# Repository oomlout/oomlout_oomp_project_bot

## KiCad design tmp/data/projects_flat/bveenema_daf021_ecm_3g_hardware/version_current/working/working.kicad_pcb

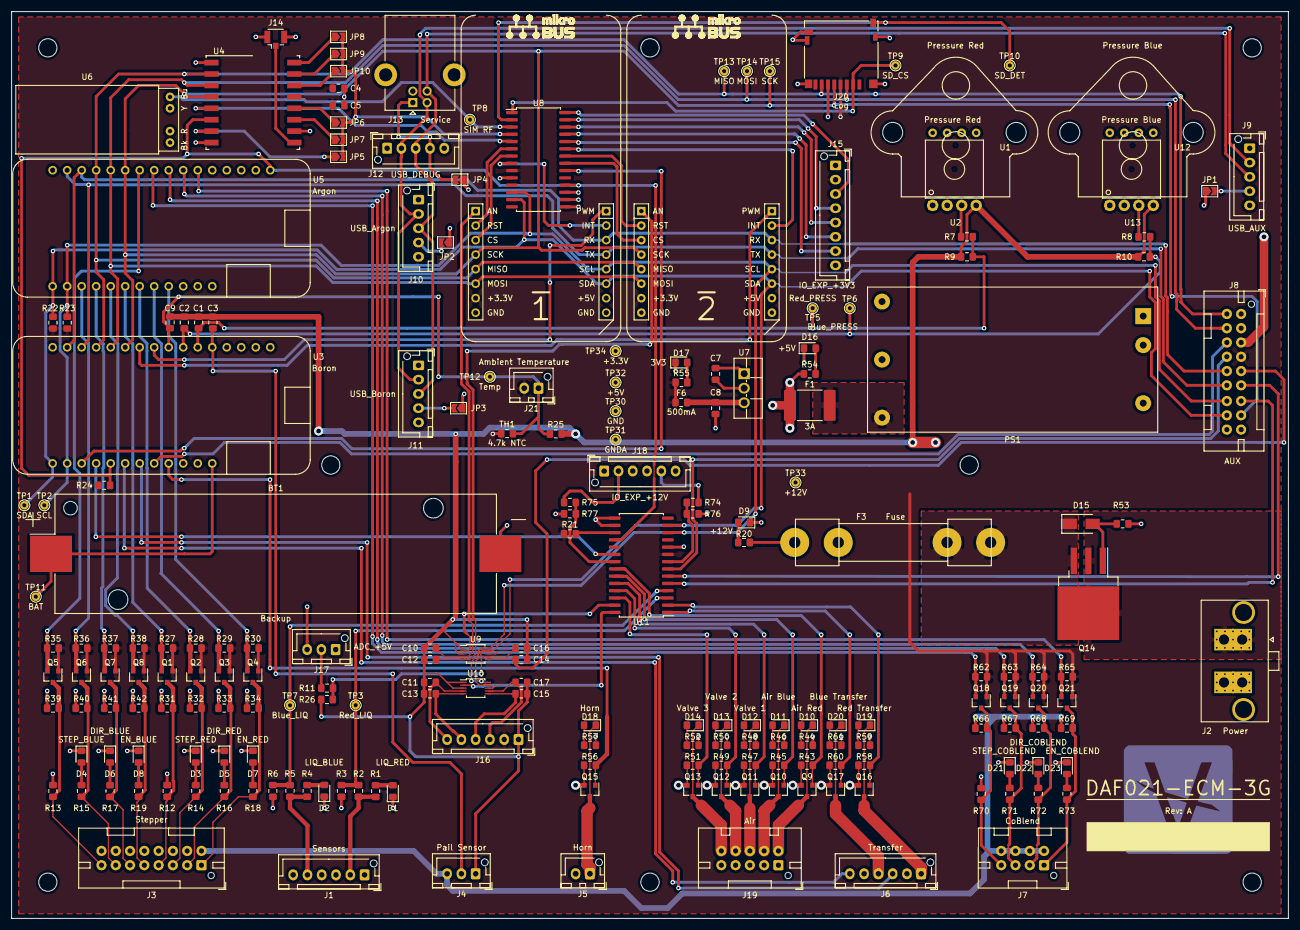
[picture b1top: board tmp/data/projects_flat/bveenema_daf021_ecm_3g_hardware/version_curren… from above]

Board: 4 copper layers, 223.5 x 158.8 mm, 207 parts (0 on the bottom side), 138 nets.

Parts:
BT1: Backup; BatteryHolder_Keystone_1042_1x18650
C1, C2, C3, C4, C9, C10, C11, C12, C13, C14, C15, C16, C17: 0.1uF; C_0805_2012Metric_Pad1.15x1.40mm_HandSolder
C5, C8: 10uF; C_0805_2012Metric_Pad1.15x1.40mm_HandSolder
C7: 2.2uF; C_0805_2012Metric_Pad1.15x1.40mm_HandSolder
D1: LIQ_RED; LED_0805_2012Metric_Pad1.15x1.40mm_HandSolder
D2: LIQ_BLUE; LED_0805_2012Metric_Pad1.15x1.40mm_HandSolder
D3: STEP_RED; LED_0805_2012Metric_Pad1.15x1.40mm_HandSolder
D4: STEP_BLUE; LED_0805_2012Metric_Pad1.15x1.40mm_HandSolder
D5: DIR_RED; LED_0805_2012Metric_Pad1.15x1.40mm_HandSolder
D6: DIR_BLUE; LED_0805_2012Metric_Pad1.15x1.40mm_HandSolder
D7: EN_RED; LED_0805_2012Metric_Pad1.15x1.40mm_HandSolder
D8: EN_BLUE; LED_0805_2012Metric_Pad1.15x1.40mm_HandSolder
D9: +12V; LED_0805_2012Metric_Pad1.15x1.40mm_HandSolder
D10: Air Red; LED_0805_2012Metric_Pad1.15x1.40mm_HandSolder
D11: Air Blue; LED_0805_2012Metric_Pad1.15x1.40mm_HandSolder
D12: Valve 1; LED_0805_2012Metric_Pad1.15x1.40mm_HandSolder
D13: Valve 2; LED_0805_2012Metric_Pad1.15x1.40mm_HandSolder
D14: Valve 3; LED_0805_2012Metric_Pad1.15x1.40mm_HandSolder
D15: 10V; D_SMA
D16: +5V; LED_0805_2012Metric_Pad1.15x1.40mm_HandSolder
D17: 3V3; LED_0805_2012Metric_Pad1.15x1.40mm_HandSolder
D18: Horn; LED_0805_2012Metric_Pad1.15x1.40mm_HandSolder
D19: Red Transfer; LED_0805_2012Metric_Pad1.15x1.40mm_HandSolder
D20: Blue Transfer; LED_0805_2012Metric_Pad1.15x1.40mm_HandSolder
D21: STEP_COBLEND; LED_0805_2012Metric_Pad1.15x1.40mm_HandSolder
D22: DIR_COBLEND; LED_0805_2012Metric_Pad1.15x1.40mm_HandSolder
D23: EN_COBLEND; LED_0805_2012Metric_Pad1.15x1.40mm_HandSolder
F1: 3A; Fuse_2920_7451Metric_Pad2.10x5.45mm_HandSolder
F3: Fuse; FUSE_HOLDER_.25inx1.25in_01220093Z
F6: 500mA; Fuse_0805_2012Metric_Pad1.15x1.40mm_HandSolder
J1: Sensors; JST_XH_B6B-XH-AM_1x06_P2.50mm_Vertical
J2: Power; Molex_Sabre_43160-2102_1x02_P7.50mm_Vertical_ThermalVias
J3: Stepper; JST_XAD_B16B-XADSS-N-A_2x08_P2.50mm_Vertical
J4: Pail Sensor; JST_XH_B3B-XH-AM_1x03_P2.50mm_Vertical
J5: Horn; JST_XH_B2B-XH-AM_1x02_P2.50mm_Vertical
J6: Transfer; JST_XH_B6B-XH-AM_1x06_P2.50mm_Vertical
J7: CoBlend; JST_XAD_B08B-XADSS-N-A_2x04_P2.50mm_Vertical
J8: AUX; JST_XAD_B18B-XADSS-N-A_2x09_P2.50mm_Vertical
J9: USB_AUX; JST_XH_B5B-XH-AM_1x05_P2.50mm_Vertical
J10: USB_Argon; JST_XH_B5B-XH-AM_1x05_P2.50mm_Vertical
J11: USB_Boron; JST_XH_B5B-XH-AM_1x05_P2.50mm_Vertical
J12: USB_DEBUG; JST_XH_B5B-XH-AM_1x05_P2.50mm_Vertical
J13: Service; USB_B_Molex_67068-8000_Horizontal
J14: Antenna; U.FL_Hirose_U.FL-R-SMT-1_Vertical
J15: IO_EXP_+3V3; JST_XH_B8B-XH-AM_1x08_P2.50mm_Vertical
J16: ADC_+3V3; JST_XH_B6B-XH-AM_1x06_P2.50mm_Vertical
J17: ADC_+5V; JST_XH_B3B-XH-AM_1x03_P2.50mm_Vertical
J18: IO_EXP_+12V; JST_XH_B6B-XH-AM_1x06_P2.50mm_Vertical
J19: Air; JST_XAD_B10B-XADSS-N-A_2x05_P2.50mm_Vertical
J20: Log; microSD_HC_Hirose_DM3D-SF
J21: Ambient Temperature; JST_XH_B2B-XH-AM_1x02_P2.50mm_Vertical
JP1, JP2, JP3, JP4, JP5, JP6, JP7, JP8, JP9, JP10: Jumper_NO_Small; SolderJumper-2_P1.3mm_Open_TrianglePad1.0x1.5mm
NT1: Net-Tie_2; NetTie-2_SMD_Pad2.0mm
PS1: 12V/5V Converter; MeanWell_Power_Supply_2x1in_Shielded
Q1, Q2, Q3, Q4, Q5, Q6, Q7, Q8, Q9, Q10, Q11, Q12, Q13, Q15, Q16, Q17, Q18, Q19, Q20, Q21: Q_NMOS_GSD; SOT-23
Q14: Q_PMOS_GDS; TO-263-3_TabPin2
R1, R4, R14, R15, R16, R17, R18, R19, R20, R54, R71, R72, R73: 4.7K; R_0805_2012Metric_Pad1.15x1.40mm_HandSolder
R2, R5, R21, R24, R74, R75: 10K; R_0805_2012Metric_Pad1.15x1.40mm_HandSolder
R3, R6, R76, R77: 1.5K; R_0805_2012Metric_Pad1.15x1.40mm_HandSolder
R7, R8, R11: 2.2k 0.5%; R_0805_2012Metric_Pad1.15x1.40mm_HandSolder
R9, R10, R25, R26: 4.7k 0.5%; R_0805_2012Metric_Pad1.15x1.40mm_HandSolder
R12, R13, R55, R70: 1k; R_0805_2012Metric_Pad1.15x1.40mm_HandSolder
R22, R23, R44, R46, R48, R50, R52, R57, R59, R61: 4.7k; R_0805_2012Metric_Pad1.15x1.40mm_HandSolder
R27, R28, R29, R30, R31, R32, R33, R34, R35, R36, R37, R38, R39, R40, R41, R42, R62, R63, R64, R65, R66, R67, R68, R69: 10k; R_0805_2012Metric_Pad1.15x1.40mm_HandSolder
R43, R45, R47, R49, R51, R53, R56, R58, R60: 100k; R_0805_2012Metric_Pad1.15x1.40mm_HandSolder
TH1: 4.7k NTC; R_0805_2012Metric_Pad1.15x1.40mm_HandSolder
TP1: SDA; TestPoint_THTPad_D1.5mm_Drill0.7mm
TP2: SCL; TestPoint_THTPad_D1.5mm_Drill0.7mm
TP3: Red_LIQ; TestPoint_THTPad_D1.5mm_Drill0.7mm
TP5: Red_PRESS; TestPoint_THTPad_D1.5mm_Drill0.7mm
TP6: Blue_PRESS; TestPoint_THTPad_D1.5mm_Drill0.7mm
TP7: Blue_LIQ; TestPoint_THTPad_D1.5mm_Drill0.7mm
TP8: SIM RF; TestPoint_THTPad_D1.5mm_Drill0.7mm
TP9: SD_CS; TestPoint_THTPad_D1.5mm_Drill0.7mm
TP10: SD_DET; TestPoint_THTPad_D1.5mm_Drill0.7mm
TP11: BAT; TestPoint_THTPad_D1.5mm_Drill0.7mm
TP12: Temp; TestPoint_THTPad_D1.5mm_Drill0.7mm
TP13: MISO; TestPoint_THTPad_D1.5mm_Drill0.7mm
TP14: MOSI; TestPoint_THTPad_D1.5mm_Drill0.7mm
TP15: SCK; TestPoint_THTPad_D1.5mm_Drill0.7mm
TP30: GND; TestPoint_THTPad_D1.5mm_Drill0.7mm
TP31: GNDA; TestPoint_THTPad_D1.5mm_Drill0.7mm
TP32: +5V; TestPoint_THTPad_D1.5mm_Drill0.7mm
TP33: +12V; TestPoint_THTPad_D1.5mm_Drill0.7mm
TP34: +3.3V; TestPoint_THTPad_D1.5mm_Drill0.7mm
U1: Pressure Red; HoneyWell_DIP_AN
U2: Pressure Red; HoneyWell_SIP_NB
U3: Boron; Argon_Boron_Xenon
U4: RFM69HCW; HOPERF_RFM69HCW
U5: Argon; Argon_Boron_Xenon
U6: AK-220V-119
U7: 5V/3V3 Regulator; TO-220F-3_Vertical
U8, U11: MCP23017; SOIC-28W_7.5x17.9mm_P1.27mm
U9, U10: ADS1115IDGS; TSSOP-10_3x3mm_P0.5mm
U12: Pressure Blue; HoneyWell_DIP_AN
U13: Pressure Blue; HoneyWell_SIP_NB

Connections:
+3V3: C4.2, C5.2, F6.1, J8.7, J15.2, J16.2, J20.4, J21.2, Q1.1, Q2.1, Q3.1, Q4.1, Q5.1, Q6.1, Q7.1, Q8.1, Q18.1, Q19.1, Q20.1, Q21.1, R21.1, R22.1, R23.1, R24.1, R27.2, R28.2, R29.2, R30.2, R35.2, R36.2, R37.2, R38.2, R55.1, R62.2, R63.2, R64.2, R65.2, TH1.1, TP34.1, U4.13, U8.9, U9.8, U10.8, U11.9
+5V: C7.2, F1.1, J3.2, J3.4, J3.6, J3.8, J3.10, J3.12, J3.14, J3.16, J4.3, J7.2, J7.4, J7.6, J7.8, J8.5, J17.3, JP1.1, JP2.1, JP3.1, JP4.1, R31.1, R32.1, R33.1, R34.1, R39.1, R40.1, R41.1, R42.1, R54.1, R66.1, R67.1, R68.1, R69.1, TP32.1, U1.2, U2.2, U3.26, U5.26, U6.R, U7.1, U12.2, U13.2
+12V: F3.2, J1.3, J1.6, J5.2, J6.2, J6.5, J8.3, J18.3, J18.6, J19.1, J19.3, J19.5, J19.7, J19.9, PS1.1, R20.1, R44.1, R46.1, R48.1, R50.1, R52.1, R57.1, R59.1, R61.1, TP33.1
/Power/VIN: J2.1, Q14.2
/Power/VIN_PROTECT: D15.1, F3.1, Q14.3
/USB(+): J9.3, J10.3, J11.3, J12.3, J13.3
/USB(-): J9.2, J10.2, J11.2, J12.2, J13.2
ADC_1_RDY: U9.2, U11.27
ADC_2_RDY: U10.2, U11.28
AUS_RST: J8.11, U11.6
AUX_AN: C14.2, J8.9, U9.6
AUX_CS: J8.13, U11.5
AUX_INT: J8.8, U11.7
AUX_PWM: J8.6, U3.24
AUX_RX: J8.10, U3.15, U5.14
AUX_TX: J8.12, U3.14, U5.15
Air_Blue_EN: Q10.1, R45.1, U11.23
Air_Blue_GND: D11.1, J19.4, Q10.3
Air_Red_EN: Q9.1, R43.1, U11.22
Air_Red_GND: D10.1, J19.2, Q9.3
Ambient_Temperature: C9.2, J21.1, R25.1, TH1.2, TP12.1, U3.8
Blue_DIR: J3.11, Q7.3, R17.1, R41.2
Blue_DIR_LV: Q7.2, R37.1, U5.20
Blue_EN: J3.9, Q8.3, R19.1, R42.2
Blue_EN_LV: Q8.2, R38.1, U5.21
Blue_STATUS: J3.15, Q5.3, R13.2, R39.2
Blue_STATUS_LV: Q5.2, R35.1, U5.10
Blue_STEP: J3.13, Q6.3, R15.1, R40.2
Blue_STEP_LV: Q6.2, R36.1, U5.19
CoBlend_DIR: J7.3, Q20.3, R68.2, R72.1
CoBlend_DIR_LV: Q20.2, R64.1, U5.7
CoBlend_EN: J7.1, Q21.3, R69.2, R73.1
CoBlend_EN_LV: Q21.2, R65.1, U5.6
CoBlend_STATUS: J7.7, Q18.3, R66.2, R70.2
CoBlend_STATUS_LV: Q18.2, R62.1, U5.9
CoBlend_STEP: J7.5, Q19.3, R67.2, R71.1
CoBlend_STEP_LV: Q19.2, R63.1, U5.8
GND: BT1.2, C4.1, C5.1, C7.1, C8.2, D1.1, D2.1, D3.1, D4.1, D5.1, D6.1, D7.1, D8.1, D9.1, D16.1, D17.1, D21.1, D22.1, D23.1, J1.1, J1.4, J2.2, J8.1, J8.17, J8.18, J9.1, J10.1, J11.1, J12.1, J13.4, J13.5, J14.2, J15.1, J17.1, J18.1, J18.4, J20.6, J20.9, J20.11, NT1.1, PS1.2, PS1.5, Q9.2, Q10.2, Q11.2, Q12.2, Q13.2, Q15.2, Q16.2, Q17.2, R3.2, R6.2, R12.1, R13.1, R43.2, R45.2, R47.2, R49.2, R51.2, R53.2, R56.2, R58.2, R60.2, R70.1, R76.2, R77.2, TP30.1, U3.4, U4.1, U4.8, U4.10, U5.4, U6.Bk, U6.Y, U7.2, U8.10, U8.15, U8.16, U8.17, U11.10, U11.15, U11.16
GNDA: C1.2, C2.2, C3.1, C9.1, C10.1, C11.1, C12.1, C13.1, C14.1, C15.1, C16.1, C17.1, J4.1, J16.1, NT1.2, R9.2, R10.2, R25.2, R26.2, TP31.1, U1.4, U2.4, U9.1, U9.3, U10.1, U10.3, U12.4, U13.4
Horn_EN: Q15.1, R56.1, U3.25
I2C_RESET: R24.2, U3.21, U4.6, U5.1, U8.18, U11.18
IO_2_INT: U3.20, U11.20
IO_INT: U3.19, U8.20
Liquid_Sensor_Blue: R5.2, R6.1, TP7.1, U11.4
Liquid_Sensor_Red: R2.2, R3.1, TP3.1, U11.3
MISO: J8.2, J20.7, TP13.1, U3.13, U4.2, U5.13
MOSI: J8.4, J20.3, TP14.1, U3.12, U4.3, U5.12
unnamed: BT1.1, TP11.1, U3.28
unnamed: C8.1, F6.2, U7.3
unnamed: C11.2, J16.6, U10.4
unnamed: C13.2, J16.5, U10.5
unnamed: C15.2, J16.4, U10.6
unnamed: C16.2, R11.1, R26.1, U9.7
unnamed: C17.2, J16.3, U10.7
unnamed: D1.2, R1.2
unnamed: D2.2, R4.2
unnamed: D3.2, R14.2
unnamed: D4.2, R15.2
unnamed: D5.2, R16.2
unnamed: D6.2, R17.2
unnamed: D7.2, R18.2
unnamed: D8.2, R19.2
unnamed: D9.2, R20.2
unnamed: D10.2, R44.2
unnamed: D11.2, R46.2
unnamed: D12.2, R48.2
unnamed: D13.2, R50.2
unnamed: D14.2, R52.2
unnamed: D15.2, Q14.1, R53.1
unnamed: D16.2, R54.2
unnamed: D17.2, R55.2
unnamed: D18.1, J5.1, Q15.3
unnamed: D18.2, R57.2
unnamed: D19.2, R59.2
unnamed: D20.2, R61.2
unnamed: D21.2, R71.2
unnamed: D22.2, R72.2
unnamed: D23.2, R73.2
unnamed: F1.2, PS1.4
unnamed: J1.2, R1.1, R2.1
unnamed: J1.5, R4.1, R5.1
unnamed: J9.4, JP1.2
unnamed: J10.4, JP2.2
unnamed: J11.4, JP3.2
unnamed: J12.4, J13.1, JP4.2
unnamed: J14.1, U4.9
unnamed: J15.3, U8.28
unnamed: J15.4, U8.27
unnamed: J15.5, U8.26
unnamed: J15.6, U8.25
unnamed: J15.7, U8.24
unnamed: J17.2, R11.2
unnamed: J18.2, R75.1
unnamed: J18.5, R74.1
unnamed: JP5.1, U4.7
unnamed: JP6.1, U4.12
unnamed: JP7.1, U4.11
unnamed: JP8.1, U4.16
unnamed: JP9.1, U4.15
unnamed: JP10.1, U4.14
unnamed: R7.2, U1.3, U2.3
unnamed: R8.2, U12.3, U13.3
unnamed: R21.2, U11.17
unnamed: R74.2, R76.1, U11.8
unnamed: R75.2, R77.1, U11.21
Pail_Sensor: C3.2, J4.2, U3.5
Pressure_Blue: C2.1, R8.1, R10.1, TP6.1, U3.7
Pressure_Red: C1.1, R7.1, R9.1, TP5.1, U3.6
RADIO_CS: U4.5, U8.5
RADIO_INT: JP5.2, JP6.2, JP7.2, JP8.2, JP9.2, JP10.2, U8.4
Red_DIR: J3.3, Q3.3, R16.1, R33.2
Red_DIR_LV: Q3.2, R29.1, U5.24
Red_EN: J3.1, Q4.3, R18.1, R34.2
Red_EN_LV: Q4.2, R30.1, U5.25
Red_STATUS: J3.7, Q1.3, R12.2, R31.2
Red_STATUS_LV: Q1.2, R27.1, U5.22
Red_STEP: J3.5, Q2.3, R14.1, R32.2
Red_STEP_LV: Q2.2, R28.1, U5.23
SCK: J8.15, J20.5, TP15.1, U3.11, U4.4, U5.11
SCL: J8.14, R23.2, TP2.1, U3.18, U5.18, U8.12, U9.10, U10.10, U11.12
SDA: J8.16, R22.2, TP1.1, U3.17, U5.17, U8.13, U9.9, U10.9, U11.13
SD_CS: J20.2, TP9.1, U8.1
SD_DET: J20.10, TP10.1, U8.2
Transfer_Blue_EN: Q17.1, R60.1, U11.1
Transfer_Blue_GND: D20.1, J6.4, Q17.3
Transfer_Blue_Reserved: J6.6, U3.22
Transfer_Red_EN: Q16.1, R58.1, U11.2
Transfer_Red_GND: D19.1, J6.1, Q16.3
Transfer_Red_Reserved: J6.3, U3.23
USER_REMOTE: TP8.1, U6.Bu, U8.3
Valve_1_EN: Q11.1, R47.1, U11.24
Valve_1_GND: D12.1, J19.6, Q11.3
Valve_2_EN: Q12.1, R49.1, U11.25
Valve_2_GND: D13.1, J19.8, Q12.3
Valve_3_EN: Q13.1, R51.1, U11.26
Valve_3_GND: D14.1, J19.10, Q13.3
mikroBUS_1_AN: C10.2, U9.4
mikroBUS_2_AN: C12.2, U9.5

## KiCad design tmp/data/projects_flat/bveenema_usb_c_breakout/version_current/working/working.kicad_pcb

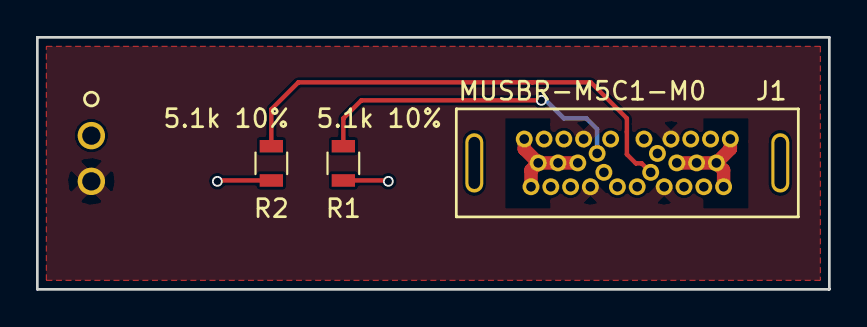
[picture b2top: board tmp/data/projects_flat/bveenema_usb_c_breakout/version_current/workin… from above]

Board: 2 copper layers, 44.0 x 14.0 mm, 4 parts (1 on the bottom side), 4 nets.

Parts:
J1: MUSBR-M5C1-M0; MUSBR-M5C1-X0
J2: 640455-2
R1, R2: 5.1k 10%; R_0805

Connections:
GND: J1.0, J1.A1, J1.A12, J1.B1, J1.B12, J1.G1, J1.G2, J1.G3, J1.G4, J1.G5, J1.G6, J2.1, R1.2, R2.2
unnamed: J1.A5, R1.1
unnamed: J1.B5, R2.1
VCC: J1.A4, J1.A9, J1.B4, J1.B9, J2.2

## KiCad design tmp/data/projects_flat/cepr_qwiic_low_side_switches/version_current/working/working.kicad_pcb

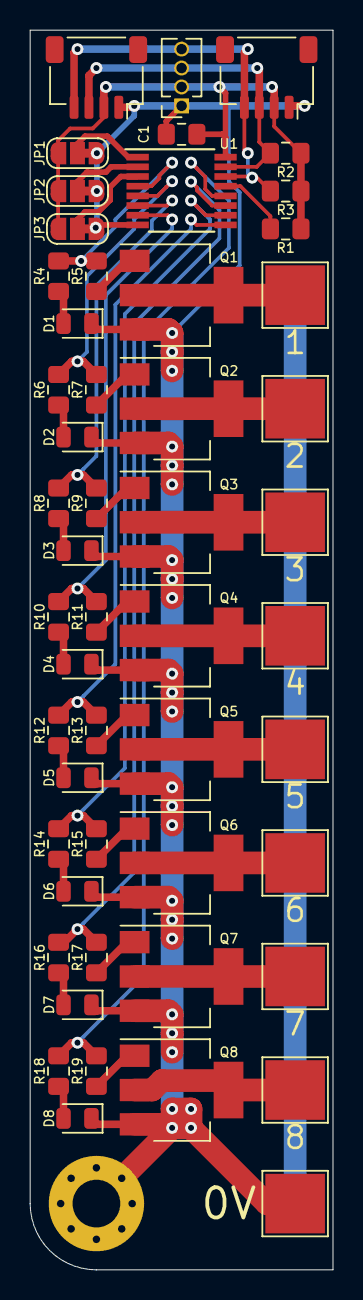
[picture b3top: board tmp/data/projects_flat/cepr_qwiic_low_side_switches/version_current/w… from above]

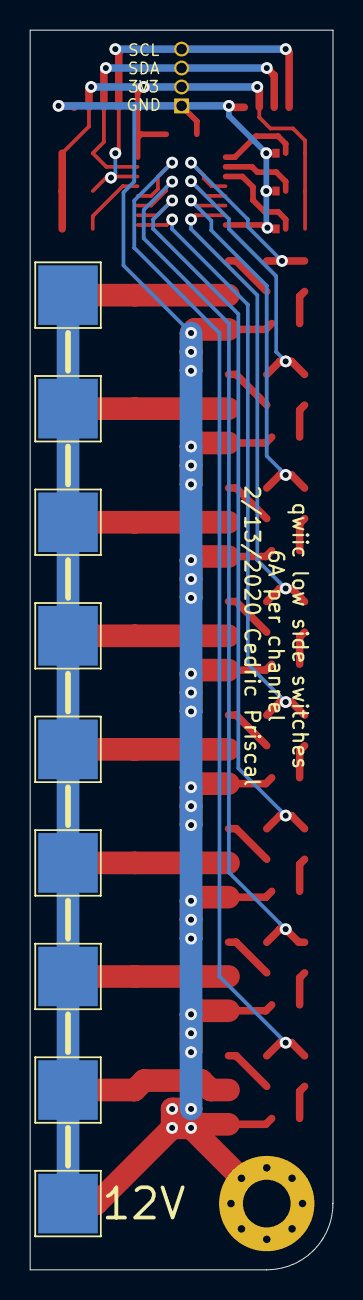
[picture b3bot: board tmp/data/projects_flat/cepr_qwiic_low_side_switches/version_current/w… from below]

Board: 2 copper layers, 20.3 x 83.2 mm, 62 parts (9 on the bottom side), 41 nets.

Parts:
C1: 0.1u; C_0805_2012Metric_Pad1.15x1.40mm_HandSolder
D1, D2, D3, D4, D5, D6, D7, D8: LITEON-LTST-C170KGKT; LED_0805_2012Metric
H2: MountingHole_Pad; MountingHole_3.2mm_M3_Pad_Via
J1, J10: Conn_01x04; JST_SH_SM04B-SRSS-TB_1x04-1MP_P1.00mm_Horizontal
J2, J3, J4, J5, J6, J7, J8, J9, J11, J12, J13, J14, J15, J16, J17, J18, J19, J20: Conn_01x01; TestPoint_Pad_4.0x4.0mm
J21: Conn_01x04; PinSocket_1x04_P1.27mm_Vertical
JP1, JP2, JP3: SolderJumper_3_Bridged12; SolderJumper-3_P1.3mm_Bridged12_RoundedPad1.0x1.5mm_NumberL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
Q1, Q2, Q3, Q4, Q5, Q6, Q7, Q8: Q_NMOS_GDSD; SOT-223
R1, R2, R3: 10k; R_0805_2012Metric_Pad1.15x1.40mm_HandSolder
R4, R5, R6, R7, R8, R9, R10, R11, R12, R13, R14, R15, R16, R17, R18, R19: 100; R_0805_2012Metric_Pad1.15x1.40mm_HandSolder
U1: PCA9534_16TSSOP; TSSOP-16_4.4x5mm_P0.65mm

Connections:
+3V3: C1.1, J1.2, J10.2, J21.2, JP1.3, JP2.3, JP3.3, R1.1, R2.1, R3.1, U1.16
/sheet5E4641D8/IN: R8.2, R9.2, U1.6
/sheet5E4641D8/OUT: J2.1, Q3.2, Q3.4
/sheet5E4641DC/IN: R10.2, R11.2, U1.7
/sheet5E4641DC/OUT: J3.1, Q4.2, Q4.4
/sheet5E46474C/IN: R16.2, R17.2, U1.11
/sheet5E46474C/OUT: J6.1, Q7.2, Q7.4
/sheet5E464087/IN: R6.2, R7.2, U1.5
/sheet5E464087/OUT: J9.1, Q2.2, Q2.4
/sheet5E464744/IN: R12.2, R13.2, U1.9
/sheet5E464744/OUT: J4.1, Q5.2, Q5.4
/sheet5E464748/IN: R14.2, R15.2, U1.10
/sheet5E464748/OUT: J5.1, Q6.2, Q6.4
/sheet5E464750/IN: R18.2, R19.2, U1.12
/sheet5E464750/OUT: J7.1, Q8.2, Q8.4
/switch-lowside-6a/IN: R4.2, R5.2, U1.4
/switch-lowside-6a/OUT: J8.1, Q1.2, Q1.4
GND: C1.2, D1.1, D2.1, D3.1, D4.1, D5.1, D6.1, D7.1, D8.1, H2.1, J1.1, J10.1, J11.1, J21.1, JP1.1, JP2.1, JP3.1, Q1.3, Q2.3, Q3.3, Q4.3, Q5.3, Q6.3, Q7.3, Q8.3, U1.8
unnamed: D1.2, R4.1
unnamed: D2.2, R6.1
unnamed: D3.2, R8.1
unnamed: D4.2, R10.1
unnamed: D5.2, R12.1
unnamed: D6.2, R14.1
unnamed: D7.2, R16.1
unnamed: D8.2, R18.1
unnamed: J12.1, J13.1, J14.1, J15.1, J16.1, J17.1, J18.1, J19.1, J20.1
unnamed: JP1.2, U1.1
unnamed: JP2.2, U1.2
unnamed: JP3.2, U1.3
unnamed: Q1.1, R5.1
unnamed: Q2.1, R7.1
unnamed: Q3.1, R9.1
unnamed: Q4.1, R11.1
unnamed: Q5.1, R13.1
unnamed: Q6.1, R15.1
unnamed: Q7.1, R17.1
unnamed: Q8.1, R19.1
unnamed: R1.2, U1.13
SCL: J1.4, J10.4, J21.4, R3.2, U1.14
SDA: J1.3, J10.3, J21.3, R2.2, U1.15

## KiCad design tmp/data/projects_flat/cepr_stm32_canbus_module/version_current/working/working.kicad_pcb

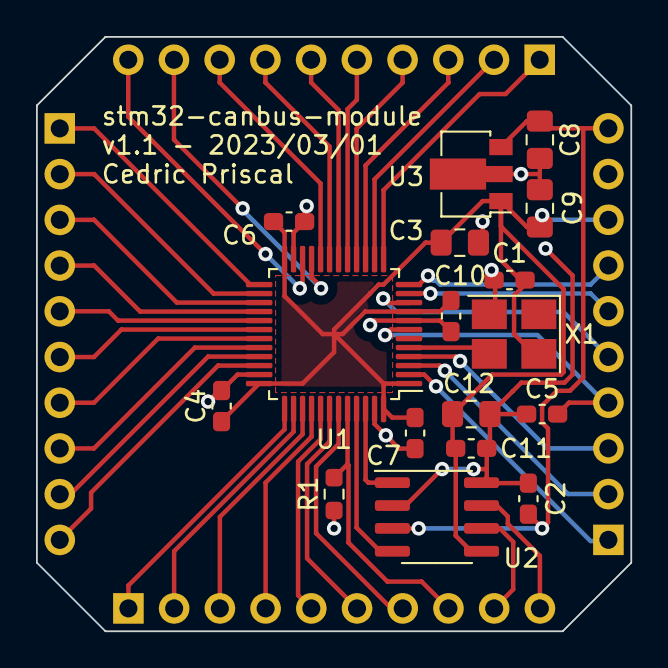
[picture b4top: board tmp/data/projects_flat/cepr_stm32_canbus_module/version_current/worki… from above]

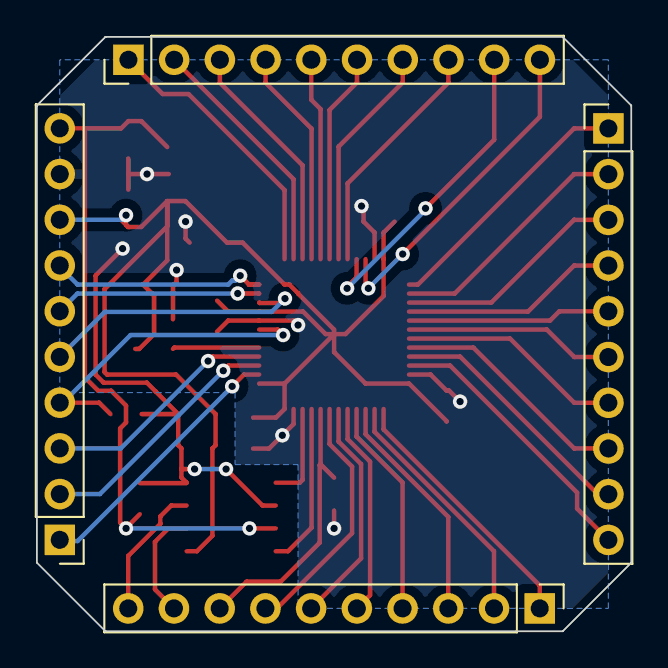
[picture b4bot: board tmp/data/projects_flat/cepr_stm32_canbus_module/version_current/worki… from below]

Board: 2 copper layers, 33.0 x 33.0 mm, 21 parts (4 on the bottom side), 43 nets.

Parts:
C1: 10nF; C_0603_1608Metric_Pad1.08x0.95mm_HandSolder
C2, C4, C5, C6, C7, C10, C11: 100nF; C_0603_1608Metric_Pad1.08x0.95mm_HandSolder
C3: 4.7uF; C_0805_2012Metric_Pad1.18x1.45mm_HandSolder
C8, C9: 1uF; C_0805_2012Metric_Pad1.18x1.45mm_HandSolder
C12: 22uF; C_0805_2012Metric_Pad1.18x1.45mm_HandSolder
J5, J6, J7, J11: Conn_01x10; PinHeader_1x10_P2.54mm_Vertical
R1: 10k; R_0603_1608Metric_Pad0.98x0.95mm_HandSolder
U1: STM32L431CCTx; LQFP-48_7x7mm_P0.5mm
U2: TLE9251; SOIC-8_3.9x4.9mm_P1.27mm
U3: AP7384-33Y; SOT-89-3
X1: ASE-8.000MHZ-LC-T; Oscillator_SMD_Abracon_ASE-4Pin_3.2x2.5mm_HandSoldering

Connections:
3V3: C1.1, C3.1, C4.1, C6.1, C7.1, C9.1, C10.1, C11.1, C12.1, J11.8, U1.1 (VBAT), U1.9 (VDDA), U1.24 (VDD), U1.36 (VDD), U1.48 (VDD), U2.5 (VIO), U3.1 (VO), X1.4 (Vdd)
5V: C2.1, C8.1, J11.10, U2.3 (VCC), U3.3 (VI)
8MHZ: U1.5 (PH0), X1.3 (OUT)
BOOT0: J7.8, R1.2, U1.44 (PH3)
CANH: J7.10, U2.7 (CANH)
CANL: J7.9, U2.6 (CANL)
CAN_RX: U1.45 (PB8), U2.4 (RXD)
CAN_TX: U1.46 (PB9), U2.1 (TXD)
GND: C1.2, C2.2, C3.2, C4.2, C5.2, C6.2, C7.2, C8.2, C9.2, C10.2, C11.2, C12.2, J11.9, R1.1, U1.8 (VSSA), U1.23 (VSS), U1.35 (VSS), U1.47 (VSS), U2.2 (GND), U2.8 (STB), U3.2 (GND), X1.2 (GND)
PA0: J11.5, U1.10 (PA0)
PA1: J11.6, U1.11 (PA1)
PA2: J11.7, U1.12 (PA2)
PA3: J5.1, U1.13 (PA3)
PA4: J5.2, U1.14 (PA4)
PA5: J5.3, U1.15 (PA5)
PA6: J5.4, U1.16 (PA6)
PA7: J5.5, U1.17 (PA7)
PA8: J6.5, U1.29 (PA8)
PA9: J6.6, U1.30 (PA9)
PA10: J6.7, U1.31 (PA10)
PA11: J6.8, U1.32 (PA11)
PA12: J6.9, U1.33 (PA12)
PA15: J7.2, U1.38 (PA15)
PB0: J5.6, U1.18 (PB0)
PB1: J5.7, U1.19 (PB1)
PB2: J5.8, U1.20 (PB2)
PB3: J7.3, U1.39 (PB3)
PB4: J7.4, U1.40 (PB4)
PB5: J7.5, U1.41 (PB5)
PB6: J7.6, U1.42 (PB6)
PB7: J7.7, U1.43 (PB7)
PB10: J5.9, U1.21 (PB10)
PB11: J5.10, U1.22 (PB11)
PB12: J6.1, U1.25 (PB12)
PB13: J6.2, U1.26 (PB13)
PB14: J6.3, U1.27 (PB14)
PB15: J6.4, U1.28 (PB15)
PC13: J11.1, U1.2 (PC13)
PC14: J11.2, U1.3 (PC14)
PC15: J11.3, U1.4 (PC15)
SWCLK: J7.1, U1.37 (PA14)
SWDIO: J6.10, U1.34 (PA13)
~RESET: C5.1, J11.4, U1.7 (NRST)

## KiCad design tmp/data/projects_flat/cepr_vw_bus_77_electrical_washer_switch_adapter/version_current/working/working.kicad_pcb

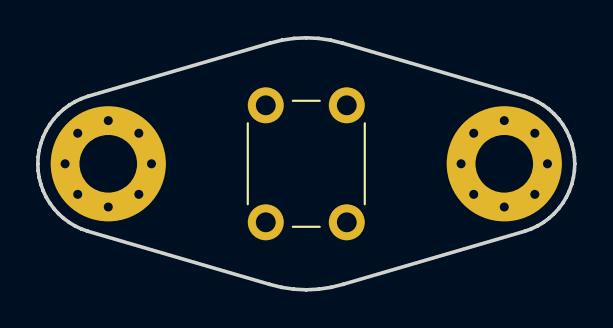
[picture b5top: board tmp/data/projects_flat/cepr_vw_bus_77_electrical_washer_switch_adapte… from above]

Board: 2 copper layers, 29.8 x 14.0 mm, 3 parts (0 on the bottom side), 2 nets, no tracks yet.

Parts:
H1, H2: MountingHole_Pad; MountingHole_3.2mm_M3_Pad_Via
SW1: SW_Push_Dual; SW_PUSH_6mm

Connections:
unnamed: H1.1, SW1.1
unnamed: H2.1, SW1.2

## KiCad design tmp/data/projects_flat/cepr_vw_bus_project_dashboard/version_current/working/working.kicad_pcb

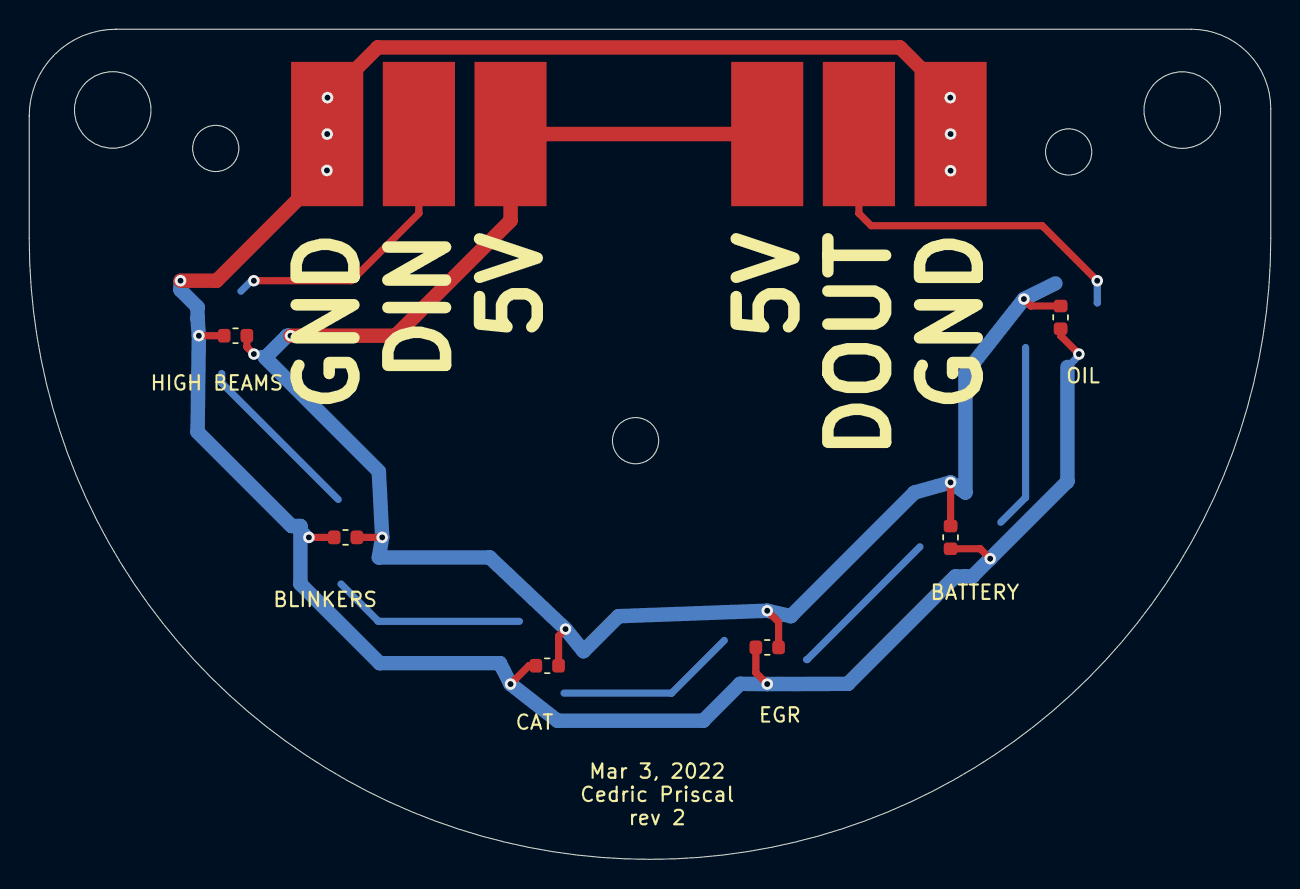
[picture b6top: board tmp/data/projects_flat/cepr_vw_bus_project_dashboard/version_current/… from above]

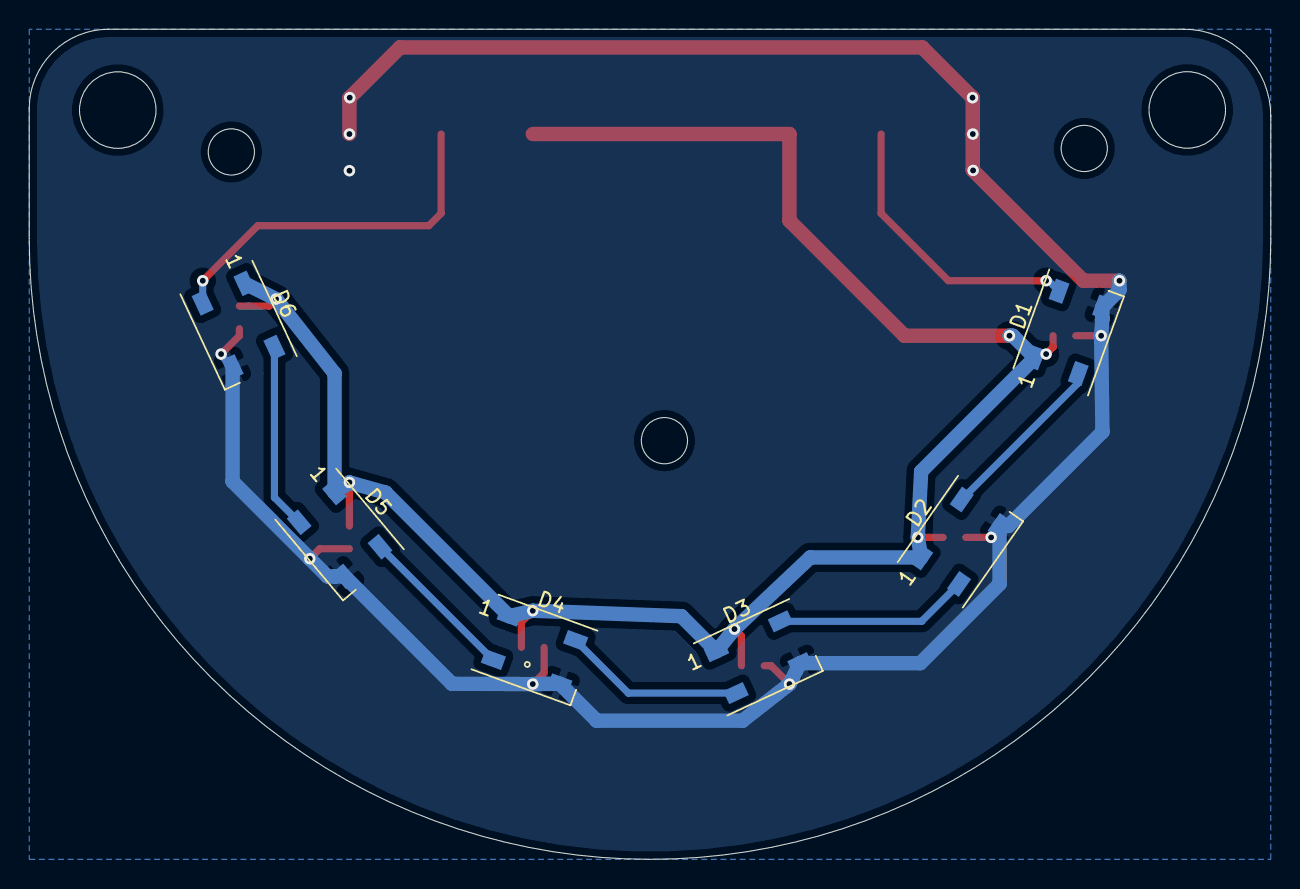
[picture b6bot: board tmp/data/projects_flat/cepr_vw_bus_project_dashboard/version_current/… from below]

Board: 2 copper layers, 86.0 x 57.5 mm, 23 parts (6 on the bottom side), 9 nets.

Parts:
C1, C2, C3, C4, C5, C6: C; C_0603_1608Metric
D1, D2, D3, D4, D5, D6: WS2812B; LED_WS2812B_PLCC4_5.0x5.0mm_P3.2mm
H1, H3: MountingHole; MountingHole_5.3mm_M5
H2, H4, H5: MountingHole; MountingHole_3.2mm_M3
J1, J2, J3, J4, J5, J6: Conn_01x01; SolderWirePad_1x01_SMD_5x10mm

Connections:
+5V: C1.1, C2.1, C3.1, C4.1, C5.1, C6.1, D1.1, D2.1, D3.1, D4.1, D5.1, D6.1, J1.1, J2.1
GND: C1.2, C2.2, C3.2, C4.2, C5.2, C6.2, D1.3, D2.3, D3.3, D4.3, D5.3, D6.3, J5.1, J6.1
unnamed: D1.2, D2.4
unnamed: D1.4, J3.1
unnamed: D2.2, D3.4
unnamed: D3.2, D4.4
unnamed: D4.2, D5.4
unnamed: D5.2, D6.4
unnamed: D6.2, J4.1

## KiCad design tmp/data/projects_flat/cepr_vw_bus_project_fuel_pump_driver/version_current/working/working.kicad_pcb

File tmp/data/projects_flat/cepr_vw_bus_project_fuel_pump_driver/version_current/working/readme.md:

# vw-bus-project-fuel-pump-driver by cepr  
This is a harvested standardized copy of a project from github.  
The original project can be found at:  
https://github.com/cepr/vw-bus-project-fuel-pump-driver  
Please consult that link for additional, details, files, and license information.  
Note: It was auto harvested and if the original repo had more than one board file or anything out of the ordinary the files here are likely not representative.

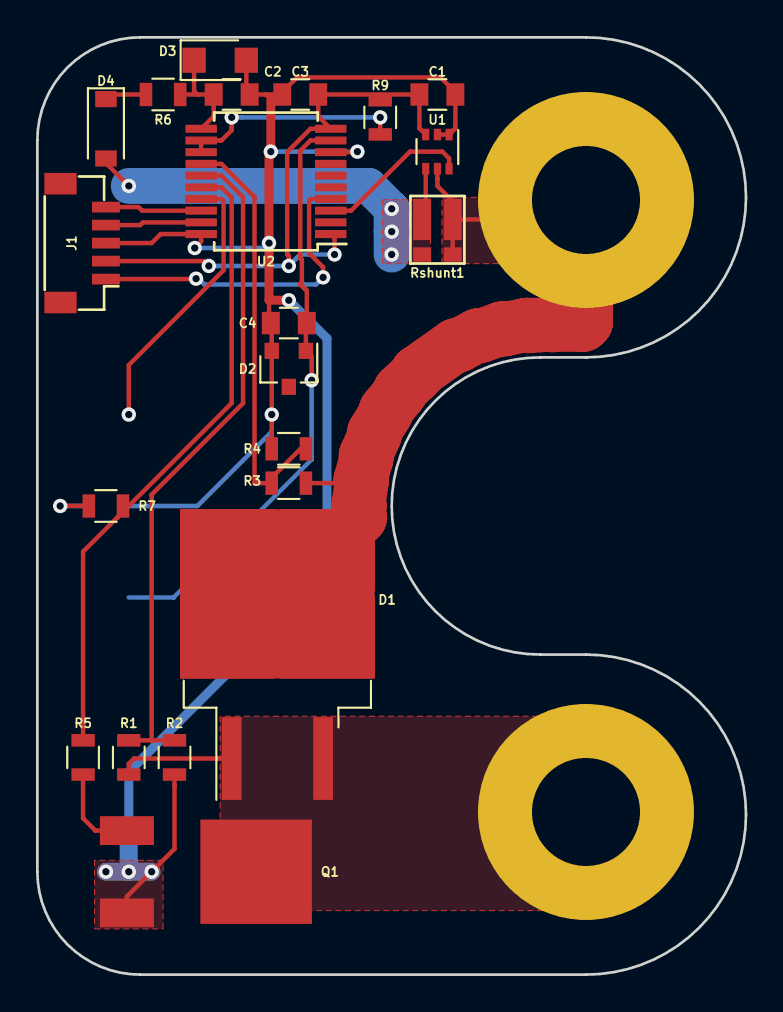
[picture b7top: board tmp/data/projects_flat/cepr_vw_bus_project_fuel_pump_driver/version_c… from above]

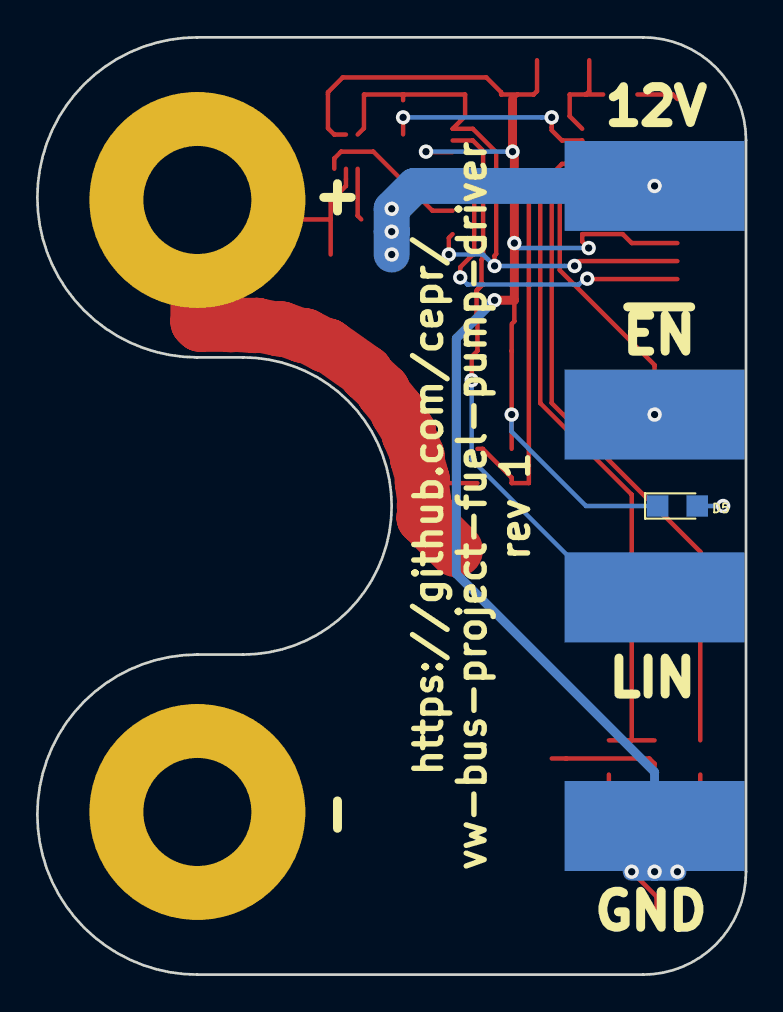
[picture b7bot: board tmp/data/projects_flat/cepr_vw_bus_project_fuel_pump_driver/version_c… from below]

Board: 2 copper layers, 39.4 x 52.1 mm, 27 parts (5 on the bottom side), 19 nets.

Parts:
C1: 100n; C_0805
C2: 22uF; C_0805
C3: 10uF; C_0805
C4: 220p; C_0805
D1: VB30100S-E3/8W; TO-263-2
D2: MMBZ27V; SOT-23
D3: D_Schottky; D_SMF
D4: 1N4148; D_SOD-123
D5: LED; LED_0805
J1: JST_BM05B-SRSS-TB(LF)(SN); JST_BM05B
J2: +12V; SolderWirePad_single_SMD_5x10mm
J3: EN; SolderWirePad_single_SMD_5x10mm
J4: LIN; SolderWirePad_single_SMD_5x10mm
J5: GND; SolderWirePad_single_SMD_5x10mm
M1: Motor_DC; fuel_pump
Q1: NCV8401BDTRKG; 369C
R1, R3: 22.1k; R_0805
R2, R4: 10.7k; R_0805
R5, R7: 150; R_0805
R6: 47; R_0805
R9: 10k; R_0805
Rshunt1: 750u; CST0612
U1: INA199x3_SC70; SOT-363_SC-70-6
U2: PIC16F1829LIN-ESS; SSOP-20_5.3x7.2mm_Pitch0.65mm

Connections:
+5V: C1.1, C3.2, J1.2, R9.2, U1.3, U2.1, U2.10
+12V: D4.2, J2.1, Rshunt1.1, U1.4
/Frontend/CURRENT_SENSE: U1.6, U2.3
/Frontend/EN: R5.2, R7.1, U2.16
/Frontend/OUT+: D1.2, M1.1, R3.1, Rshunt1.2, U1.5
/Frontend/OUT+SENSE: R3.2, R4.1, U2.14
/Frontend/OUT-: D1.1, D1.3, M1.2, Q1.2, R1.1
/Frontend/OUT-SENSE: R1.2, R2.1, U2.15
/MCU/EXT_EN: J3.1, U2.17
/MCU/ICSPCLK: J1.5, U2.18
/MCU/ICSPDAT: J1.4, U2.19
/MCU/LIN: C4.1, D2.1, J4.1, U2.9
/MCU/~MCLR: J1.1, U2.4
GND: C1.2, C2.2, C3.1, C4.2, D2.2, D3.2, D5.1, J1.3, J5.1, Q1.3, R2.2, R4.2, U1.1, U1.2, U2.8, U2.20
unnamed: C2.1, D3.1, R6.2, U2.11
unnamed: D4.1, R6.1
unnamed: D5.2, R7.2
unnamed: Q1.1, R5.1
unnamed: R9.1, U2.12, U2.13

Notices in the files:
parts and their libraries:
Copyright 2016 Accelerated Designs. All rights reserved.
